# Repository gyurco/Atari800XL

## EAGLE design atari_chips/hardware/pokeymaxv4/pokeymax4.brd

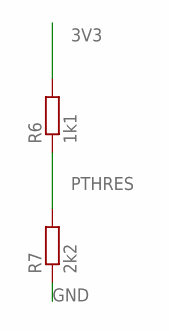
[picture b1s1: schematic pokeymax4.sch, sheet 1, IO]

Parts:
R6: 1k1; R0402
R7: 2k2; R0402

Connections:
3V3: R6.2; also elsewhere on the board
GND: R7.1; also elsewhere on the board
PTHRES: R6.1, R7.2; also elsewhere on the board

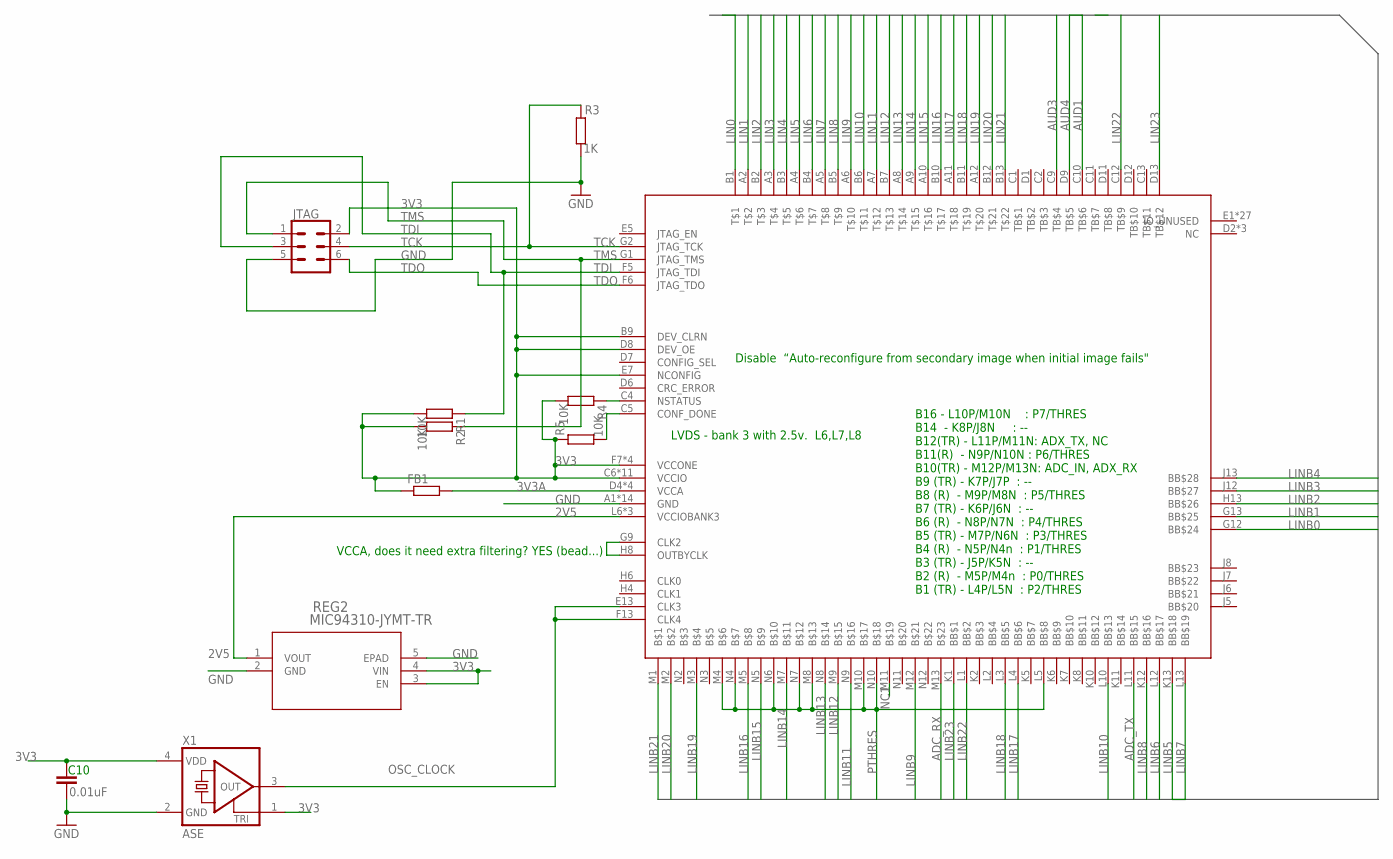
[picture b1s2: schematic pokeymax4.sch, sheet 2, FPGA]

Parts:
C10: 0.01uF; C0402
FB1: R-EU_R0402; R0402
JTAG: CONN_03X2LOCK; 2X3_LOCK
R1, R2, R4, R5: 10K; R0402
R3: 1K; R0402
REG2: MIC94310-JYMT-TR; TDFN4_1P2X1P6_MCH
U3: MAX10; U169SMALL
X1: ASE

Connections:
2V5: REG2.1 (VOUT), U3.L6 (VCCIOBANK3), U3.L7 (VCCIOBANK3), U3.L8 (VCCIOBANK3); also elsewhere on the board
3V3: C10.1, FB1.1, JTAG.2, R1.2, R2.2, R4.2, R5.1, REG2.3 (EN), REG2.4 (VIN), U3.B9 (DEV_CLRN), U3.C6 (VCCIO), U3.C7 (VCCIO), U3.C8 (VCCIO), U3.D8 (DEV_OE), U3.E7 (NCONFIG), U3.F2 (VCCIO), U3.F7 (VCCONE), U3.F11 (VCCIO), U3.G3 (VCCIO), U3.G6 (VCCONE), U3.G8 (VCCONE), U3.G11 (VCCIO), U3.H7 (VCCONE), U3.H11 (VCCIO), U3.J3 (VCCIO), U3.J11 (VCCIO), U3.K3 (VCCIO), X1.1 (TRI), X1.4 (VDD); also elsewhere on the board
3V3A: FB1.2, U3.D4 (VCCA), U3.D10 (VCCA), U3.K4 (VCCA), U3.K9 (VCCA); also elsewhere on the board
ADC_RX: U3.M13; also elsewhere on the board
ADC_TX: U3.L11 (BB$15); also elsewhere on the board
AUD1: U3.C10 (TB$6); also elsewhere on the board
AUD3: U3.C9 (TB$4); also elsewhere on the board
AUD4: U3.D9 (TB$5); also elsewhere on the board
CONF_DONE: R5.2, U3.C5 (CONF_DONE)
FAKE_CLK: U3.G9 (CLK2), U3.H8 (OUTBYCLK)
GND: C10.2, JTAG.5, R3.2, REG2.2 (GND), REG2.5 (EPAD), U3.A1 (GND), U3.A13 (GND), U3.B8 (GND), U3.C3 (GND), U3.D5 (GND), U3.E11 (GND), U3.F3 (GND), U3.G7 (GND), U3.H12 (GND), U3.J4 (GND), U3.L9 (GND), U3.M6 (GND), U3.N1 (GND), U3.N13 (GND), X1.2 (GND); also elsewhere on the board
LIN0: U3.B1; also elsewhere on the board
LIN1: U3.A2; also elsewhere on the board
LIN2: U3.B2; also elsewhere on the board
LIN3: U3.A3; also elsewhere on the board
LIN4: U3.B3; also elsewhere on the board
LIN5: U3.A4; also elsewhere on the board
LIN6: U3.B4; also elsewhere on the board
LIN7: U3.A5; also elsewhere on the board
LIN8: U3.B5; also elsewhere on the board
LIN9: U3.A6; also elsewhere on the board
LIN10: U3.B6; also elsewhere on the board
LIN11: U3.A7; also elsewhere on the board
LIN12: U3.B7; also elsewhere on the board
LIN13: U3.A8; also elsewhere on the board
LIN14: U3.A9; also elsewhere on the board
LIN15: U3.A10; also elsewhere on the board
LIN16: U3.B10; also elsewhere on the board
LIN17: U3.A11; also elsewhere on the board
LIN18: U3.B11; also elsewhere on the board
LIN19: U3.A12; also elsewhere on the board
LIN20: U3.B12; also elsewhere on the board
LIN21: U3.B13; also elsewhere on the board
LIN22: U3.C12 (TB$9); also elsewhere on the board
LIN23: U3.D13 (TB$12); also elsewhere on the board
LINB0: U3.G12 (BB$24); also elsewhere on the board
LINB1: U3.G13 (BB$25); also elsewhere on the board
LINB2: U3.H13 (BB$26); also elsewhere on the board
LINB3: U3.J12 (BB$27); also elsewhere on the board
LINB4: U3.J13 (BB$28); also elsewhere on the board
LINB5: U3.K13 (BB$18); also elsewhere on the board
LINB6: U3.L12 (BB$17); also elsewhere on the board
LINB7: U3.L13 (BB$19); also elsewhere on the board
LINB8: U3.K12 (BB$16); also elsewhere on the board
LINB9: U3.M12; also elsewhere on the board
LINB10: U3.L10 (BB$13); also elsewhere on the board
LINB11: U3.N9; also elsewhere on the board
LINB12: U3.M9; also elsewhere on the board
LINB13: U3.N8; also elsewhere on the board
LINB14: U3.M7; also elsewhere on the board
LINB15: U3.N5; also elsewhere on the board
LINB16: U3.M5; also elsewhere on the board
LINB17: U3.L4 (BB$6); also elsewhere on the board
LINB18: U3.L3 (BB$5); also elsewhere on the board
LINB19: U3.M3; also elsewhere on the board
LINB20: U3.M2; also elsewhere on the board
LINB21: U3.M1; also elsewhere on the board
LINB22: U3.L1 (BB$2); also elsewhere on the board
LINB23: U3.K1 (BB$1); also elsewhere on the board
NC1: U3.M11
NSTATUS: R4.1, U3.C4 (NSTATUS)
OSC_CLOCK: U3.E13 (CLK3), U3.F13 (CLK4), X1.3 (OUT)
PTHRES: U3.L5 (BB$8), U3.M4, U3.M8, U3.M10, U3.N4, U3.N6, U3.N7, U3.N10; also elsewhere on the board
TCK: JTAG.4, R3.1, U3.G2 (JTAG_TCK)
TDI: JTAG.3, R1.1, U3.F5 (JTAG_TDI)
TDO: JTAG.6, U3.F6 (JTAG_TDO)
TMS: JTAG.1, R2.1, U3.G1 (JTAG_TMS)

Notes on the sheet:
VCCA, does it need extra filtering? YES (bead...)
Disable “Auto-reconfigure from secondary image when initial image fails"
LVDS - bank 3 with 2.5v. L6,L7,L8
B16 - L10P/M10N : P7/THRES B14 - K8P/J8N : -- B12(TR) - L11P/M11N: ADX_TX, NC B11(R) - N9P/N10N : P6/THRES B10(TR) - M12P/M13N: ADC_IN, ADX_RX B9 (TR) - K7P/J7P : -- B8 (R) - M9P/M8N : P5/THRES B7 (TR) - K6P/J6N : -- B6 (R) - N8P/N7N : P4/THRES B5 (TR) - M7P/N6N : P3/THRES B4 (R) - N5P/N4n : P1/THR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

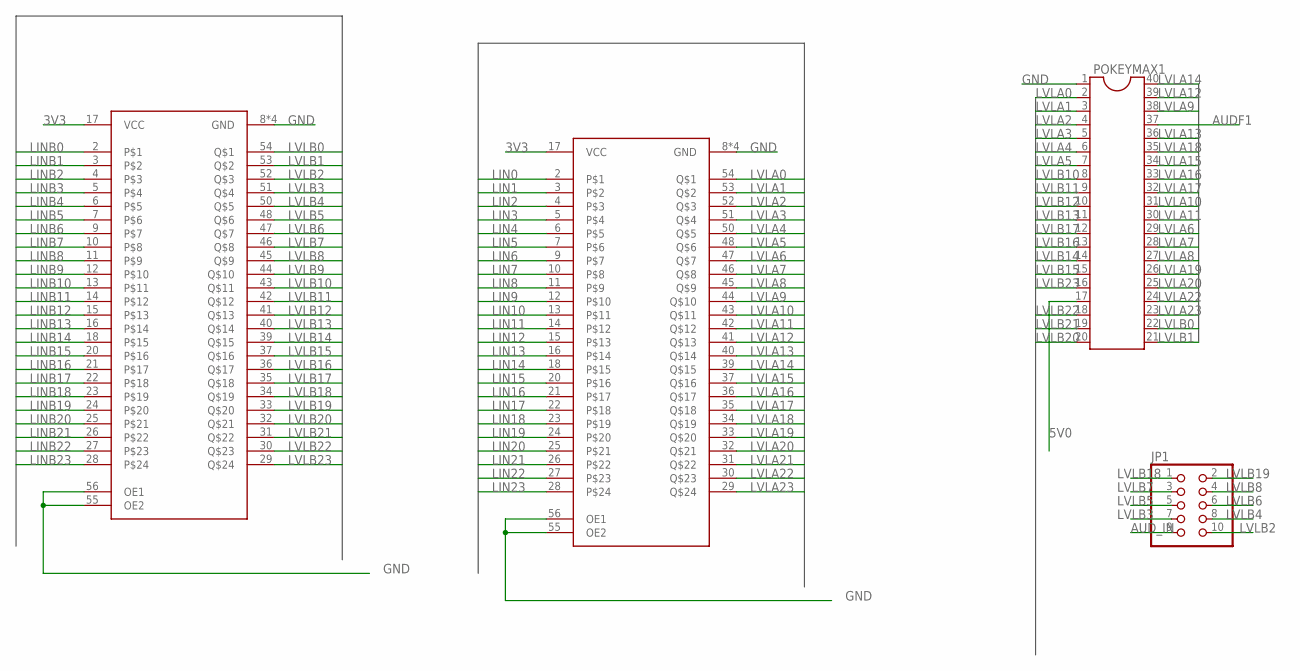
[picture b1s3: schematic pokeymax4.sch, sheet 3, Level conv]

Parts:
JP1: PINHD-2X5; 2X05
POKEYMAX1: DIL40
U2, U4: SN74CB3T16211SM; 56TVSOP_SMALL

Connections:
3V3: U2.17 (VCC), U4.17 (VCC); also elsewhere on the board
5V0: POKEYMAX1.17; also elsewhere on the board
AUDF1: POKEYMAX1.37; also elsewhere on the board
AUD_IN: JP1.9; also elsewhere on the board
GND: POKEYMAX1.1, U2.8 (GND), U2.19 (GND), U2.38 (GND), U2.49 (GND), U2.55 (OE2), U2.56 (OE1), U4.8 (GND), U4.19 (GND), U4.38 (GND), U4.49 (GND), U4.55 (OE2), U4.56 (OE1); also elsewhere on the board
LIN0: U2.2; also elsewhere on the board
LIN1: U2.3; also elsewhere on the board
LIN2: U2.4; also elsewhere on the board
LIN3: U2.5; also elsewhere on the board
LIN4: U2.6; also elsewhere on the board
LIN5: U2.7; also elsewhere on the board
LIN6: U2.9; also elsewhere on the board
LIN7: U2.10; also elsewhere on the board
LIN8: U2.11; also elsewhere on the board
LIN9: U2.12; also elsewhere on the board
LIN10: U2.13; also elsewhere on the board
LIN11: U2.14; also elsewhere on the board
LIN12: U2.15; also elsewhere on the board
LIN13: U2.16; also elsewhere on the board
LIN14: U2.18; also elsewhere on the board
LIN15: U2.20; also elsewhere on the board
LIN16: U2.21; also elsewhere on the board
LIN17: U2.22; also elsewhere on the board
LIN18: U2.23; also elsewhere on the board
LIN19: U2.24; also elsewhere on the board
LIN20: U2.25; also elsewhere on the board
LIN21: U2.26; also elsewhere on the board
LIN22: U2.27; also elsewhere on the board
LIN23: U2.28; also elsewhere on the board
LINB0: U4.2; also elsewhere on the board
LINB1: U4.3; also elsewhere on the board
LINB2: U4.4; also elsewhere on the board
LINB3: U4.5; also elsewhere on the board
LINB4: U4.6; also elsewhere on the board
LINB5: U4.7; also elsewhere on the board
LINB6: U4.9; also elsewhere on the board
LINB7: U4.10; also elsewhere on the board
LINB8: U4.11; also elsewhere on the board
LINB9: U4.12; also elsewhere on the board
LINB10: U4.13; also elsewhere on the board
LINB11: U4.14; also elsewhere on the board
LINB12: U4.15; also elsewhere on the board
LINB13: U4.16; also elsewhere on the board
LINB14: U4.18; also elsewhere on the board
LINB15: U4.20; also elsewhere on the board
LINB16: U4.21; also elsewhere on the board
LINB17: U4.22; also elsewhere on the board
LINB18: U4.23; also elsewhere on the board
LINB19: U4.24; also elsewhere on the board
LINB20: U4.25; also elsewhere on the board
LINB21: U4.26; also elsewhere on the board
LINB22: U4.27; also elsewhere on the board
LINB23: U4.28; also elsewhere on the board
LVLA0: POKEYMAX1.2, U2.54
LVLA1: POKEYMAX1.3, U2.53
LVLA2: POKEYMAX1.4, U2.52
LVLA3: POKEYMAX1.5, U2.51
LVLA4: POKEYMAX1.6, U2.50
LVLA5: POKEYMAX1.7, U2.48
LVLA6: POKEYMAX1.29, U2.47
LVLA7: POKEYMAX1.28, U2.46
LVLA8: POKEYMAX1.27, U2.45
LVLA9: POKEYMAX1.38, U2.44
LVLA10: POKEYMAX1.31, U2.43
LVLA11: POKEYMAX1.30, U2.42
LVLA12: POKEYMAX1.39, U2.41
LVLA13: POKEYMAX1.36, U2.40
LVLA14: POKEYMAX1.40, U2.39
LVLA15: POKEYMAX1.34, U2.37
LVLA16: POKEYMAX1.33, U2.36
LVLA17: POKEYMAX1.32, U2.35
LVLA18: POKEYMAX1.35, U2.34
LVLA19: POKEYMAX1.26, U2.33
LVLA20: POKEYMAX1.25, U2.32
LVLA21: U2.31; also elsewhere on the board
LVLA22: POKEYMAX1.24, U2.30
LVLA23: POKEYMAX1.23, U2.29
LVLB0: POKEYMAX1.22, U4.54
LVLB1: POKEYMAX1.21, U4.53
LVLB2: JP1.10, U4.52
LVLB3: JP1.7, U4.51
LVLB4: JP1.8, U4.50
LVLB5: JP1.5, U4.48
LVLB6: JP1.6, U4.47
LVLB7: JP1.3, U4.46
LVLB8: JP1.4, U4.45
LVLB9: U4.44; also elsewhere on the board
LVLB10: POKEYMAX1.8, U4.43
LVLB11: POKEYMAX1.9, U4.42
LVLB12: POKEYMAX1.10, U4.41
LVLB13: POKEYMAX1.11, U4.40
LVLB14: POKEYMAX1.14, U4.39
LVLB15: POKEYMAX1.15, U4.37
LVLB16: POKEYMAX1.13, U4.36
LVLB17: POKEYMAX1.12, U4.35
LVLB18: JP1.1, U4.34
LVLB19: JP1.2, U4.33
LVLB20: POKEYMAX1.20, U4.32
LVLB21: POKEYMAX1.19, U4.31
LVLB22: POKEYMAX1.18, U4.30
LVLB23: POKEYMAX1.16, U4.29

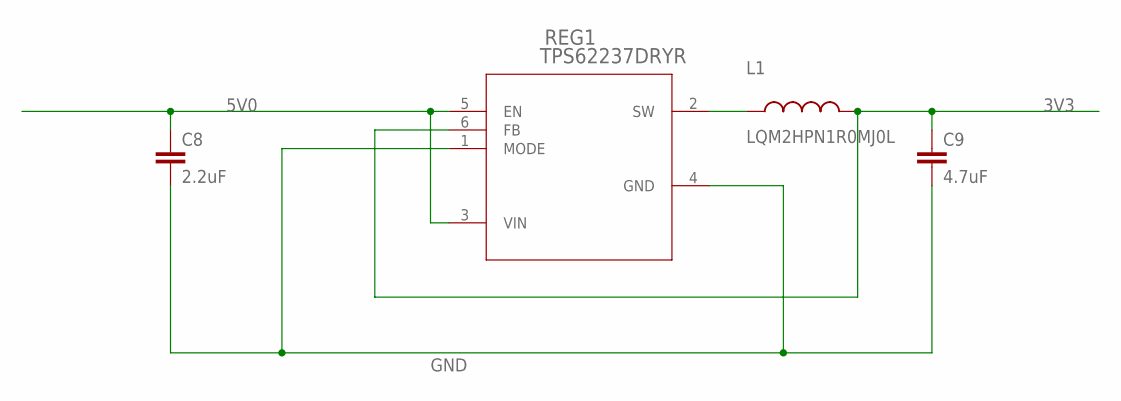
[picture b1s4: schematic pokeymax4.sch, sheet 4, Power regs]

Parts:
C8: 2.2uF; C0402
C9: 4.7uF; C0402
L1: LQM2HPN1R0MJ0L; INDC1008X04
REG1: TPS62237DRYR; DRY6

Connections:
3V3: C9.1, L1.2, REG1.6 (FB); also elsewhere on the board
5V0: C8.1, REG1.3 (VIN), REG1.5 (EN); also elsewhere on the board
GND: C8.2, C9.2, REG1.1 (MODE), REG1.4 (GND); also elsewhere on the board
unnamed: L1.1, REG1.2 (SW)

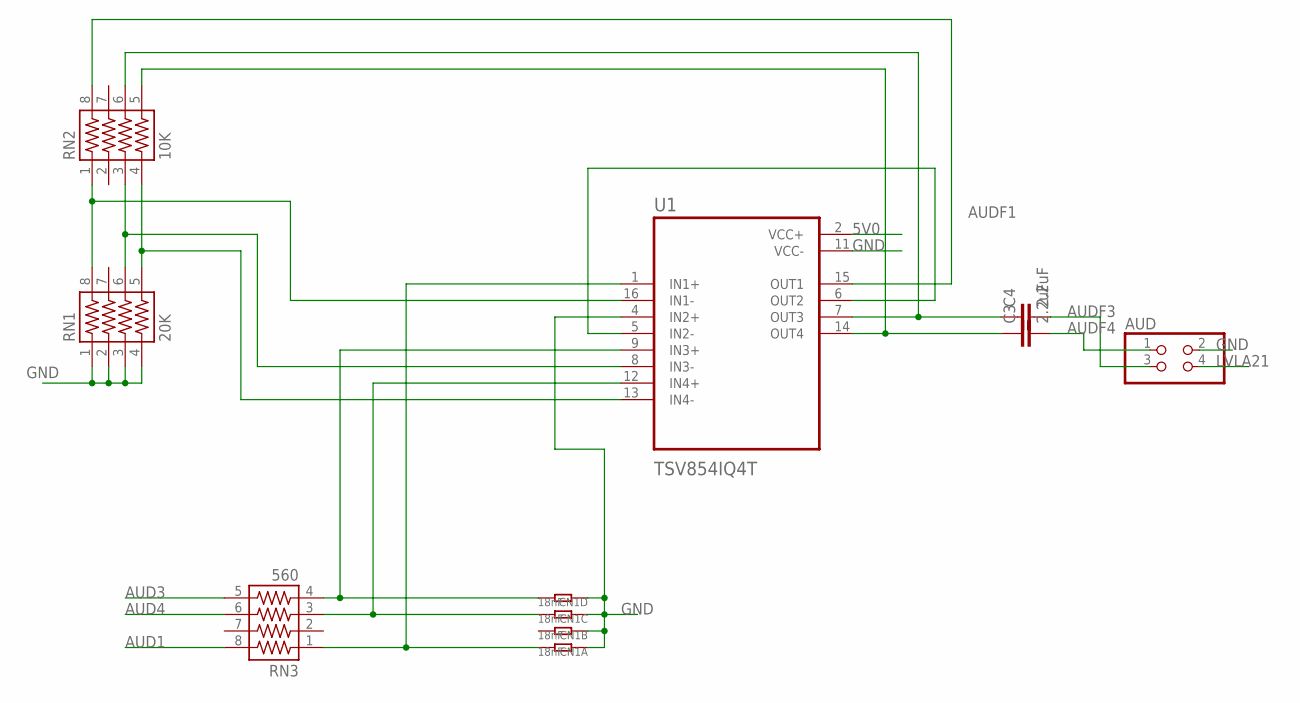
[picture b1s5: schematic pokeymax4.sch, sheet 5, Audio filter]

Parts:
AUD: PINHD-2X2; 2X02
C3, C4: 2.2uF; C0402
CN1: 18nF; R1206-8
RN1: 20K; 741-8
RN2: 10K; 741-8
RN3: 560; 741-8
U1: TSV854IQ4T; QFN50P300X300X100-16N

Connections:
5V0: U1.2 (VCC+); also elsewhere on the board
AMPIN1M: RN1.8, RN2.1, U1.16 (IN1-)
AMPIN1P: CN1.8 (2), RN3.1, U1.1 (IN1+)
AMPIN3M: RN1.6, RN2.3, U1.8 (IN3-)
AMPIN3P: CN1.5 (2), RN3.4, U1.9 (IN3+)
AMPIN4P: CN1.6 (2), RN3.3, U1.12 (IN4+)
AUD1: RN3.8; also elsewhere on the board
AUD3: RN3.5; also elsewhere on the board
AUD4: RN3.6; also elsewhere on the board
AUDF1: RN2.8, U1.15 (OUT1); also elsewhere on the board
AUDF2: U1.5 (IN2-), U1.6 (OUT2)
AUDF3: AUD.3, C4.2
AUDF4: AUD.1, C3.2
GND: AUD.2, CN1.1, CN1.2 (1), CN1.3 (1), CN1.4 (1), RN1.1, RN1.2, RN1.3, RN1.4, U1.4 (IN2+), U1.11 (VCC-); also elsewhere on the board
LVLA21: AUD.4; also elsewhere on the board
unnamed: C3.1, RN2.5, U1.14 (OUT4)
unnamed: C4.1, RN2.6, U1.7 (OUT3)
unnamed: RN1.5, RN2.4, U1.13 (IN4-)

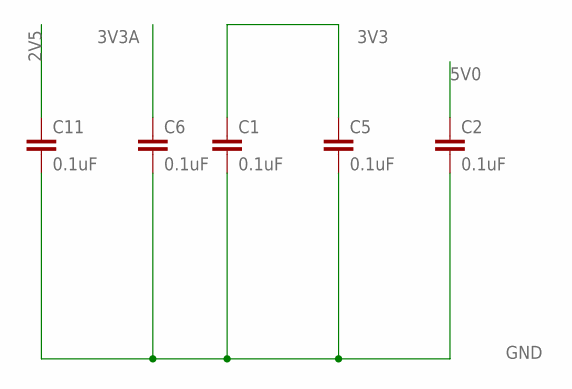
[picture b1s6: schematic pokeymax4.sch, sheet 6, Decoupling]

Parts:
C1, C2, C5, C6, C11: 0.1uF; C0402

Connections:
2V5: C11.1; also elsewhere on the board
3V3: C1.1, C5.1; also elsewhere on the board
3V3A: C6.1; also elsewhere on the board
5V0: C2.1; also elsewhere on the board
GND: C1.2, C2.2, C5.2, C6.2, C11.2; also elsewhere on the board

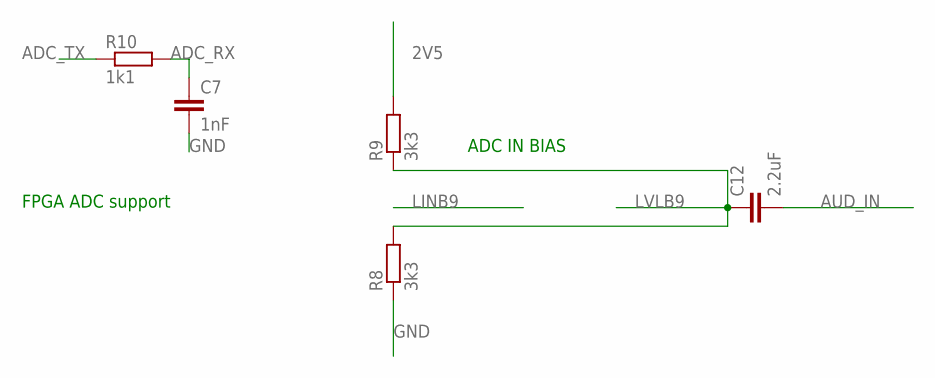
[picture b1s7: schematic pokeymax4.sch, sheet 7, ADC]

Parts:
C7: 1nF; C0402
C12: 2.2uF; C0402
R8, R9: 3k3; R0402
R10: 1k1; R0402

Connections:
2V5: R9.2; also elsewhere on the board
ADC_RX: C7.1, R10.2; also elsewhere on the board
ADC_TX: R10.1; also elsewhere on the board
AUD_IN: C12.2; also elsewhere on the board
GND: C7.2, R8.1; also elsewhere on the board
LVLB9: C12.1, R8.2, R9.1; also elsewhere on the board

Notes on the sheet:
ADC IN BIAS
FPGA ADC support

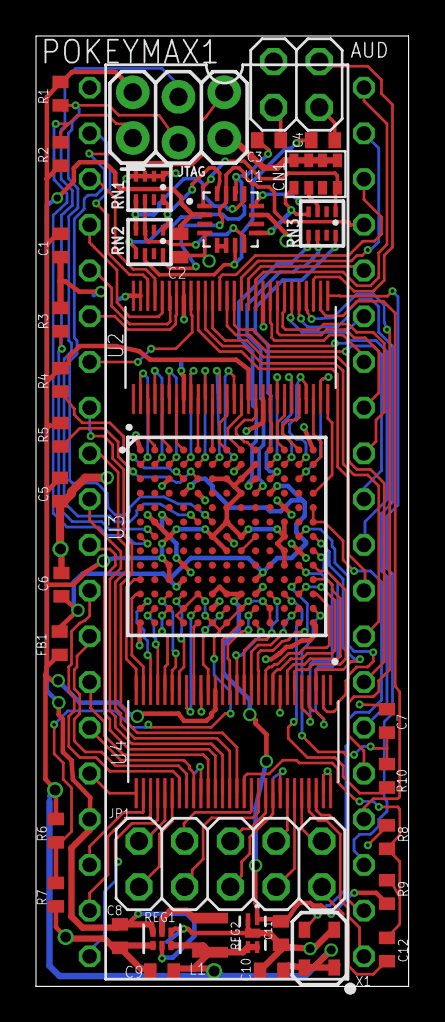
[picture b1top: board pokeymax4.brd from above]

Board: 4 copper layers, 20.7 x 52.8 mm, 39 parts (0 on the bottom side), 129 nets.

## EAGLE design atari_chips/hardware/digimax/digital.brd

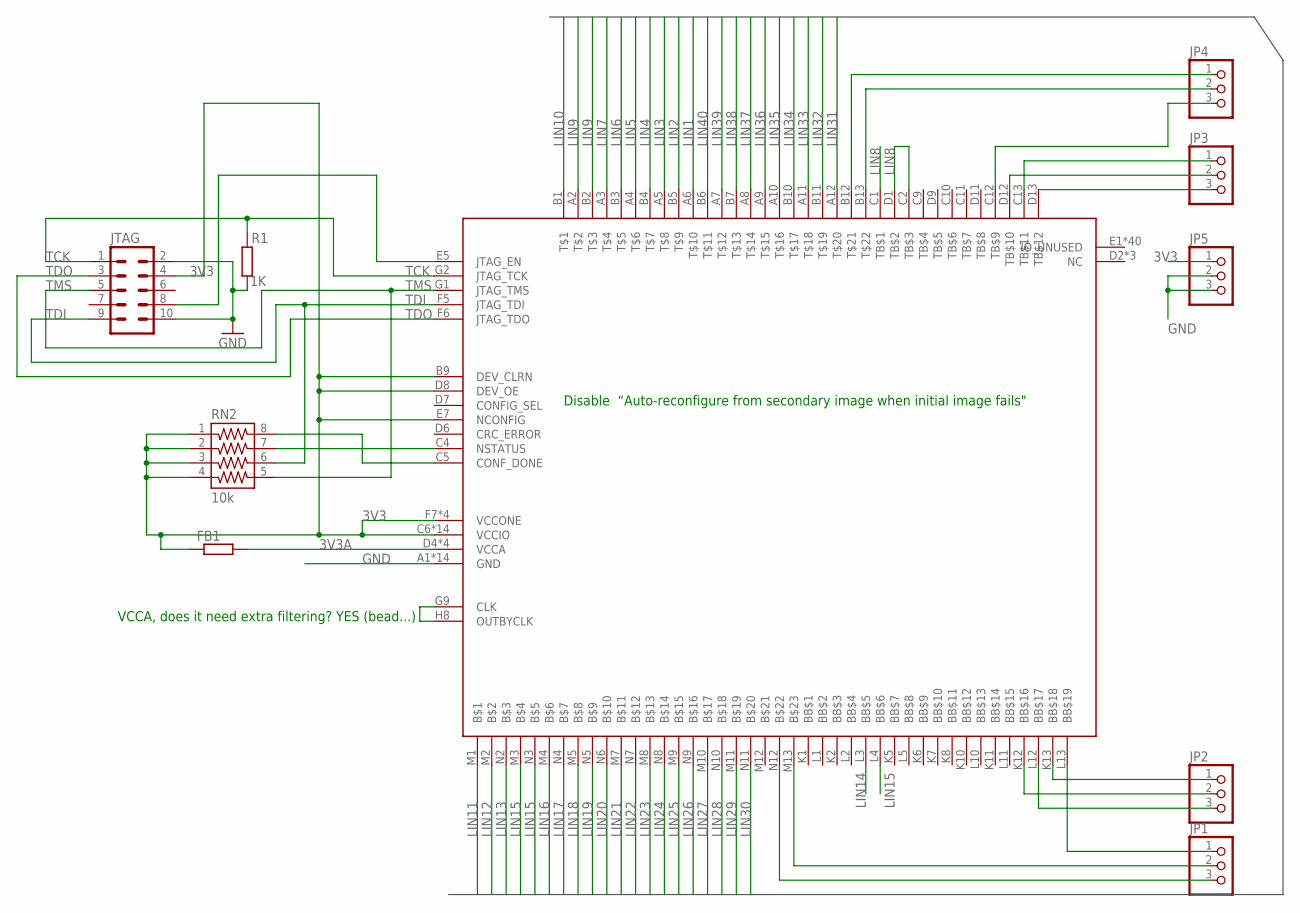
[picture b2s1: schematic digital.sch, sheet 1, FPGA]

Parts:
FB1: R-EU_R0603; R0603
JP1, JP2, JP3, JP4, JP5: PINHD-1X3; 1X03
JTAG: ML10
MAX10: MAX10; U169SMALL
R1: 1K; R0603
RN2: 10k; 742-8

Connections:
3V3: FB1.1, JP5.1, JTAG.4, MAX10.B9 (DEV_CLRN), MAX10.C6 (VCCIO), MAX10.C7 (VCCIO), MAX10.C8 (VCCIO), MAX10.D8 (DEV_OE), MAX10.E7 (NCONFIG), MAX10.F2 (VCCIO), MAX10.F7 (VCCONE), MAX10.F11 (VCCIO), MAX10.G3 (VCCIO), MAX10.G6 (VCCONE), MAX10.G8 (VCCONE), MAX10.G11 (VCCIO), MAX10.H7 (VCCONE), MAX10.H11 (VCCIO), MAX10.J3 (VCCIO), MAX10.J11 (VCCIO), MAX10.K3 (VCCIO), MAX10.L6 (VCCIO), MAX10.L7 (VCCIO), MAX10.L8 (VCCIO), RN2.1, RN2.2, RN2.3, RN2.4; also elsewhere on the board
3V3A: FB1.2, MAX10.D4 (VCCA), MAX10.D10 (VCCA), MAX10.K4 (VCCA), MAX10.K9 (VCCA); also elsewhere on the board
CONF_DONE: MAX10.C5 (CONF_DONE), RN2.8
FAKE_CLK: MAX10.G9 (CLK), MAX10.H8 (OUTBYCLK)
GND: JP5.2, JP5.3, JTAG.2, JTAG.10, MAX10.A1 (GND), MAX10.A13 (GND), MAX10.B8 (GND), MAX10.C3 (GND), MAX10.D5 (GND), MAX10.E11 (GND), MAX10.F3 (GND), MAX10.G7 (GND), MAX10.H12 (GND), MAX10.J4 (GND), MAX10.L9 (GND), MAX10.M6 (GND), MAX10.N1 (GND), MAX10.N13 (GND), R1.2; also elsewhere on the board
JTAGEN: JTAG.8, MAX10.E5 (JTAG_EN)
LIN1: MAX10.A6; also elsewhere on the board
LIN2: MAX10.B5; also elsewhere on the board
LIN3: MAX10.A5; also elsewhere on the board
LIN4: MAX10.B4; also elsewhere on the board
LIN5: MAX10.A4; also elsewhere on the board
LIN6: MAX10.B3; also elsewhere on the board
LIN7: MAX10.A3; also elsewhere on the board
LIN8: MAX10.C1 (TB$1), MAX10.C2 (TB$3), MAX10.D1 (TB$2); also elsewhere on the board
LIN9: MAX10.A2, MAX10.B2; also elsewhere on the board
LIN10: MAX10.B1; also elsewhere on the board
LIN11: MAX10.M1; also elsewhere on the board
LIN12: MAX10.M2; also elsewhere on the board
LIN13: MAX10.N2; also elsewhere on the board
LIN14: MAX10.L3 (BB$5); also elsewhere on the board
LIN15: MAX10.L4 (BB$6), MAX10.M3, MAX10.N3; also elsewhere on the board
LIN16: MAX10.M4; also elsewhere on the board
LIN17: MAX10.N4; also elsewhere on the board
LIN18: MAX10.M5; also elsewhere on the board
LIN19: MAX10.N5; also elsewhere on the board
LIN20: MAX10.N6; also elsewhere on the board
LIN21: MAX10.M7; also elsewhere on the board
LIN22: MAX10.N7; also elsewhere on the board
LIN23: MAX10.M8; also elsewhere on the board
LIN24: MAX10.N8; also elsewhere on the board
LIN25: MAX10.M9; also elsewhere on the board
LIN26: MAX10.N9; also elsewhere on the board
LIN27: MAX10.M10; also elsewhere on the board
LIN28: MAX10.N10; also elsewhere on the board
LIN29: MAX10.M11; also elsewhere on the board
LIN30: MAX10.N11; also elsewhere on the board
LIN31: MAX10.A12; also elsewhere on the board
LIN32: MAX10.B11; also elsewhere on the board
LIN33: MAX10.A11; also elsewhere on the board
LIN34: MAX10.B10; also elsewhere on the board
LIN35: MAX10.A10; also elsewhere on the board
LIN36: MAX10.A9; also elsewhere on the board
LIN37: MAX10.A8; also elsewhere on the board
LIN38: MAX10.B7; also elsewhere on the board
LIN39: MAX10.A7; also elsewhere on the board
LIN40: MAX10.B6; also elsewhere on the board
unnamed: JP2.2, MAX10.K12 (BB$16)
unnamed: JP1.3, MAX10.N12
unnamed: JP1.2, MAX10.M13
unnamed: JP2.1, MAX10.K13 (BB$18)
unnamed: JP2.3, MAX10.L12 (BB$17)
unnamed: JP1.1, MAX10.L13 (BB$19)
unnamed: JP3.3, MAX10.D13 (TB$12)
unnamed: JP3.1, MAX10.C13 (TB$11)
unnamed: JP3.2, MAX10.D12 (TB$10)
unnamed: JP4.3, MAX10.C12 (TB$9)
unnamed: JP4.2, MAX10.B13
unnamed: JP4.1, MAX10.B12
NSTATUS: MAX10.C4 (NSTATUS), RN2.7
TCK: JTAG.1, MAX10.G2 (JTAG_TCK), R1.1
TDI: JTAG.9, MAX10.F5 (JTAG_TDI), RN2.6
TDO: JTAG.3, MAX10.F6 (JTAG_TDO)
TMS: JTAG.5, MAX10.G1 (JTAG_TMS), RN2.5

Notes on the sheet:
VCCA, does it need extra filtering? YES (bead...)
Disable “Auto-reconfigure from secondary image when initial image fails"

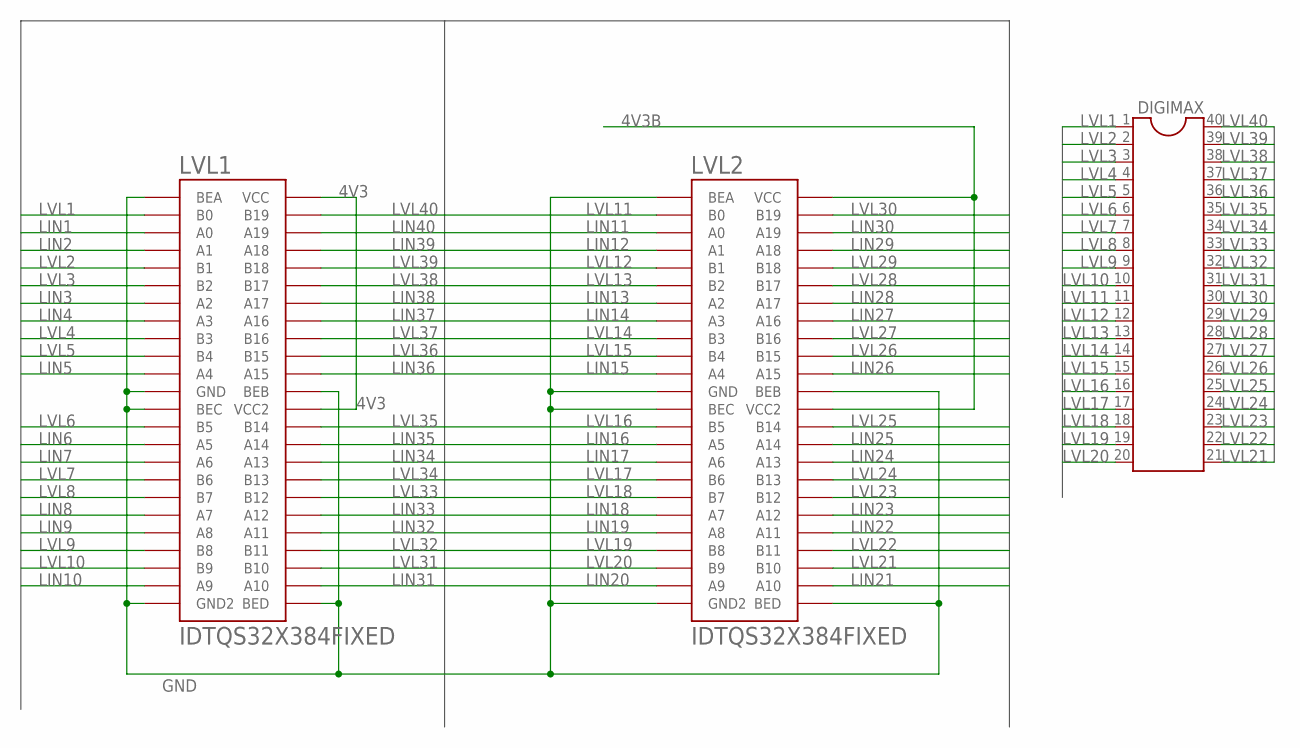
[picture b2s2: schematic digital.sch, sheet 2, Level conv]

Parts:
DIGIMAX: DIL40
LVL1, LVL2: IDTQS32X384FIXED; IDTQS32X384_04MM

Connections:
4V3: LVL1.P$36 (VCC2), LVL1.P$48 (VCC); also elsewhere on the board
4V3B: LVL2.P$36 (VCC2), LVL2.P$48 (VCC); also elsewhere on the board
GND: LVL1.P$1 (BEA), LVL1.P$12 (GND), LVL1.P$13 (BEC), LVL1.P$24 (GND2), LVL1.P$25 (BED), LVL1.P$37 (BEB), LVL2.P$1 (BEA), LVL2.P$12 (GND), LVL2.P$13 (BEC), LVL2.P$24 (GND2), LVL2.P$25 (BED), LVL2.P$37 (BEB); also elsewhere on the board
LIN1: LVL1.P$3 (A0); also elsewhere on the board
LIN2: LVL1.P$4 (A1); also elsewhere on the board
LIN3: LVL1.P$7 (A2); also elsewhere on the board
LIN4: LVL1.P$8 (A3); also elsewhere on the board
LIN5: LVL1.P$11 (A4); also elsewhere on the board
LIN6: LVL1.P$15 (A5); also elsewhere on the board
LIN7: LVL1.P$16 (A6); also elsewhere on the board
LIN8: LVL1.P$19 (A7); also elsewhere on the board
LIN9: LVL1.P$20 (A8); also elsewhere on the board
LIN10: LVL1.P$23 (A9); also elsewhere on the board
LIN11: LVL2.P$3 (A0); also elsewhere on the board
LIN12: LVL2.P$4 (A1); also elsewhere on the board
LIN13: LVL2.P$7 (A2); also elsewhere on the board
LIN14: LVL2.P$8 (A3); also elsewhere on the board
LIN15: LVL2.P$11 (A4); also elsewhere on the board
LIN16: LVL2.P$15 (A5); also elsewhere on the board
LIN17: LVL2.P$16 (A6); also elsewhere on the board
LIN18: LVL2.P$19 (A7); also elsewhere on the board
LIN19: LVL2.P$20 (A8); also elsewhere on the board
LIN20: LVL2.P$23 (A9); also elsewhere on the board
LIN21: LVL2.P$26 (A10); also elsewhere on the board
LIN22: LVL2.P$29 (A11); also elsewhere on the board
LIN23: LVL2.P$30 (A12); also elsewhere on the board
LIN24: LVL2.P$33 (A13); also elsewhere on the board
LIN25: LVL2.P$34 (A14); also elsewhere on the board
LIN26: LVL2.P$38 (A15); also elsewhere on the board
LIN27: LVL2.P$41 (A16); also elsewhere on the board
LIN28: LVL2.P$42 (A17); also elsewhere on the board
LIN29: LVL2.P$45 (A18); also elsewhere on the board
LIN30: LVL2.P$46 (A19); also elsewhere on the board
LIN31: LVL1.P$26 (A10); also elsewhere on the board
LIN32: LVL1.P$29 (A11); also elsewhere on the board
LIN33: LVL1.P$30 (A12); also elsewhere on the board
LIN34: LVL1.P$33 (A13); also elsewhere on the board
LIN35: LVL1.P$34 (A14); also elsewhere on the board
LIN36: LVL1.P$38 (A15); also elsewhere on the board
LIN37: LVL1.P$41 (A16); also elsewhere on the board
LIN38: LVL1.P$42 (A17); also elsewhere on the board
LIN39: LVL1.P$45 (A18); also elsewhere on the board
LIN40: LVL1.P$46 (A19); also elsewhere on the board
LVL1: DIGIMAX.1, LVL1.P$2 (B0)
LVL2: DIGIMAX.2, LVL1.P$5 (B1)
LVL3: DIGIMAX.3, LVL1.P$6 (B2)
LVL4: DIGIMAX.4, LVL1.P$9 (B3)
LVL5: DIGIMAX.5, LVL1.P$10 (B4)
LVL6: DIGIMAX.6, LVL1.P$14 (B5)
LVL7: DIGIMAX.7, LVL1.P$17 (B6)
LVL8: DIGIMAX.8, LVL1.P$18 (B7)
LVL9: DIGIMAX.9, LVL1.P$21 (B8)
LVL10: DIGIMAX.10, LVL1.P$22 (B9)
LVL11: DIGIMAX.11, LVL2.P$2 (B0)
LVL12: DIGIMAX.12, LVL2.P$5 (B1)
LVL13: DIGIMAX.13, LVL2.P$6 (B2)
LVL14: DIGIMAX.14, LVL2.P$9 (B3)
LVL15: DIGIMAX.15, LVL2.P$10 (B4)
LVL16: DIGIMAX.16, LVL2.P$14 (B5)
LVL17: DIGIMAX.17, LVL2.P$17 (B6)
LVL18: DIGIMAX.18, LVL2.P$18 (B7)
LVL19: DIGIMAX.19, LVL2.P$21 (B8)
LVL20: DIGIMAX.20, LVL2.P$22 (B9)
LVL21: DIGIMAX.21, LVL2.P$27 (B10)
LVL22: DIGIMAX.22, LVL2.P$28 (B11)
LVL23: DIGIMAX.23, LVL2.P$31 (B12)
LVL24: DIGIMAX.24, LVL2.P$32 (B13)
LVL25: DIGIMAX.25, LVL2.P$35 (B14)
LVL26: DIGIMAX.26, LVL2.P$39 (B15)
LVL27: DIGIMAX.27, LVL2.P$40 (B16)
LVL28: DIGIMAX.28, LVL2.P$43 (B17)
LVL29: DIGIMAX.29, LVL2.P$44 (B18)
LVL30: DIGIMAX.30, LVL2.P$47 (B19)
LVL31: DIGIMAX.31, LVL1.P$27 (B10)
LVL32: DIGIMAX.32, LVL1.P$28 (B11)
LVL33: DIGIMAX.33, LVL1.P$31 (B12)
LVL34: DIGIMAX.34, LVL1.P$32 (B13)
LVL35: DIGIMAX.35, LVL1.P$35 (B14)
LVL36: DIGIMAX.36, LVL1.P$39 (B15)
LVL37: DIGIMAX.37, LVL1.P$40 (B16)
LVL38: DIGIMAX.38, LVL1.P$43 (B17)
LVL39: DIGIMAX.39, LVL1.P$44 (B18)
LVL40: DIGIMAX.40, LVL1.P$47 (B19)

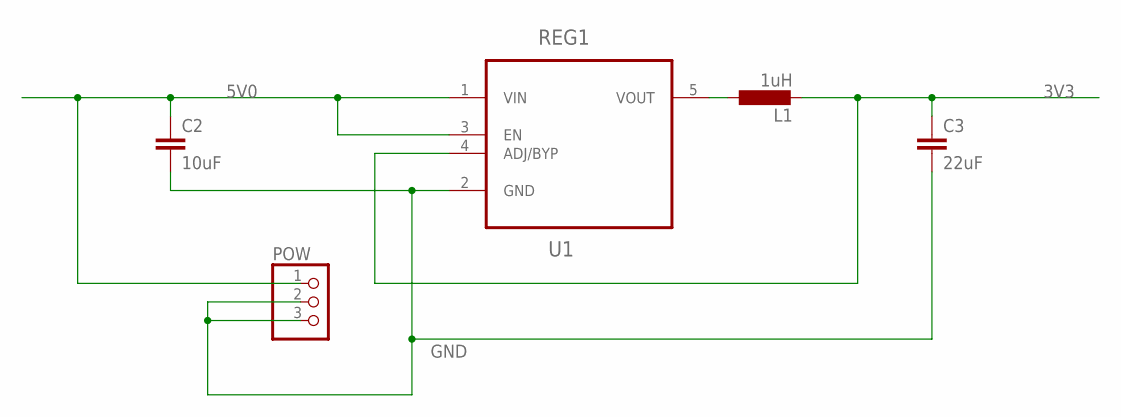
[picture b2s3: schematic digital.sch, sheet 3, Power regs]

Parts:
C2: 10uF; C0805
C3: 22uF; C0805
L1: 1uH; L3225M
POW: PINHD-1X3; 1X03
REG1: U1; SOT95P280X145-5N

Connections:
3V3: C3.1, L1.2, REG1.4 (ADJ/BYP); also elsewhere on the board
5V0: C2.1, POW.1, REG1.1 (VIN), REG1.3 (EN); also elsewhere on the board
GND: C2.2, C3.2, POW.2, POW.3, REG1.2 (GND); also elsewhere on the board
unnamed: L1.1, REG1.5 (VOUT)

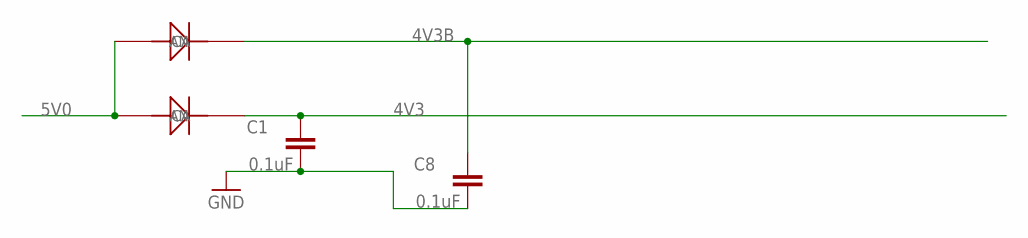
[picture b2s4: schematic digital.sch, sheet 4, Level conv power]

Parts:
C1, C8: 0.1uF; C0603
D1, D2: 1N4148; SOD123

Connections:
4V3: C1.2, D1.1 (CA); also elsewhere on the board
4V3B: C8.2, D2.1 (CA); also elsewhere on the board
5V0: D1.2 (AN), D2.2 (AN); also elsewhere on the board
GND: C1.1, C8.1; also elsewhere on the board

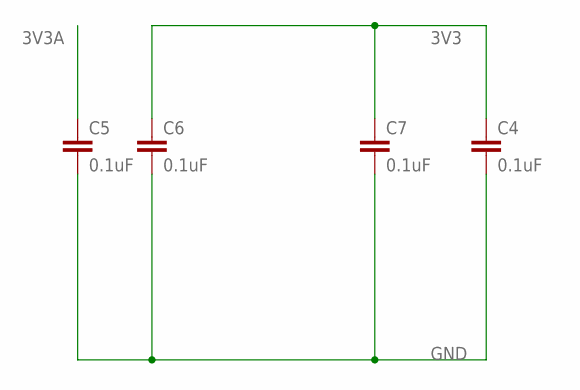
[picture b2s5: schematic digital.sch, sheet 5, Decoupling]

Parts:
C4, C5, C6, C7: 0.1uF; C0603

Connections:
3V3: C4.1, C6.1, C7.1; also elsewhere on the board
3V3A: C5.1; also elsewhere on the board
GND: C4.2, C5.2, C6.2, C7.2; also elsewhere on the board

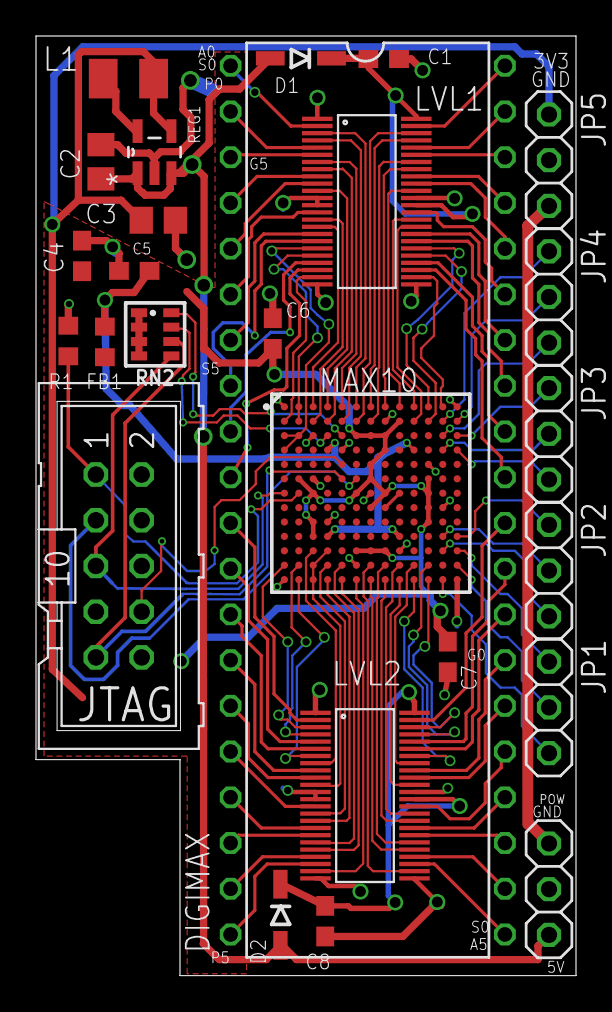
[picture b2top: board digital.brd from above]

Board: 2 copper layers, 30.0 x 52.2 mm, 26 parts (0 on the bottom side), 107 nets.

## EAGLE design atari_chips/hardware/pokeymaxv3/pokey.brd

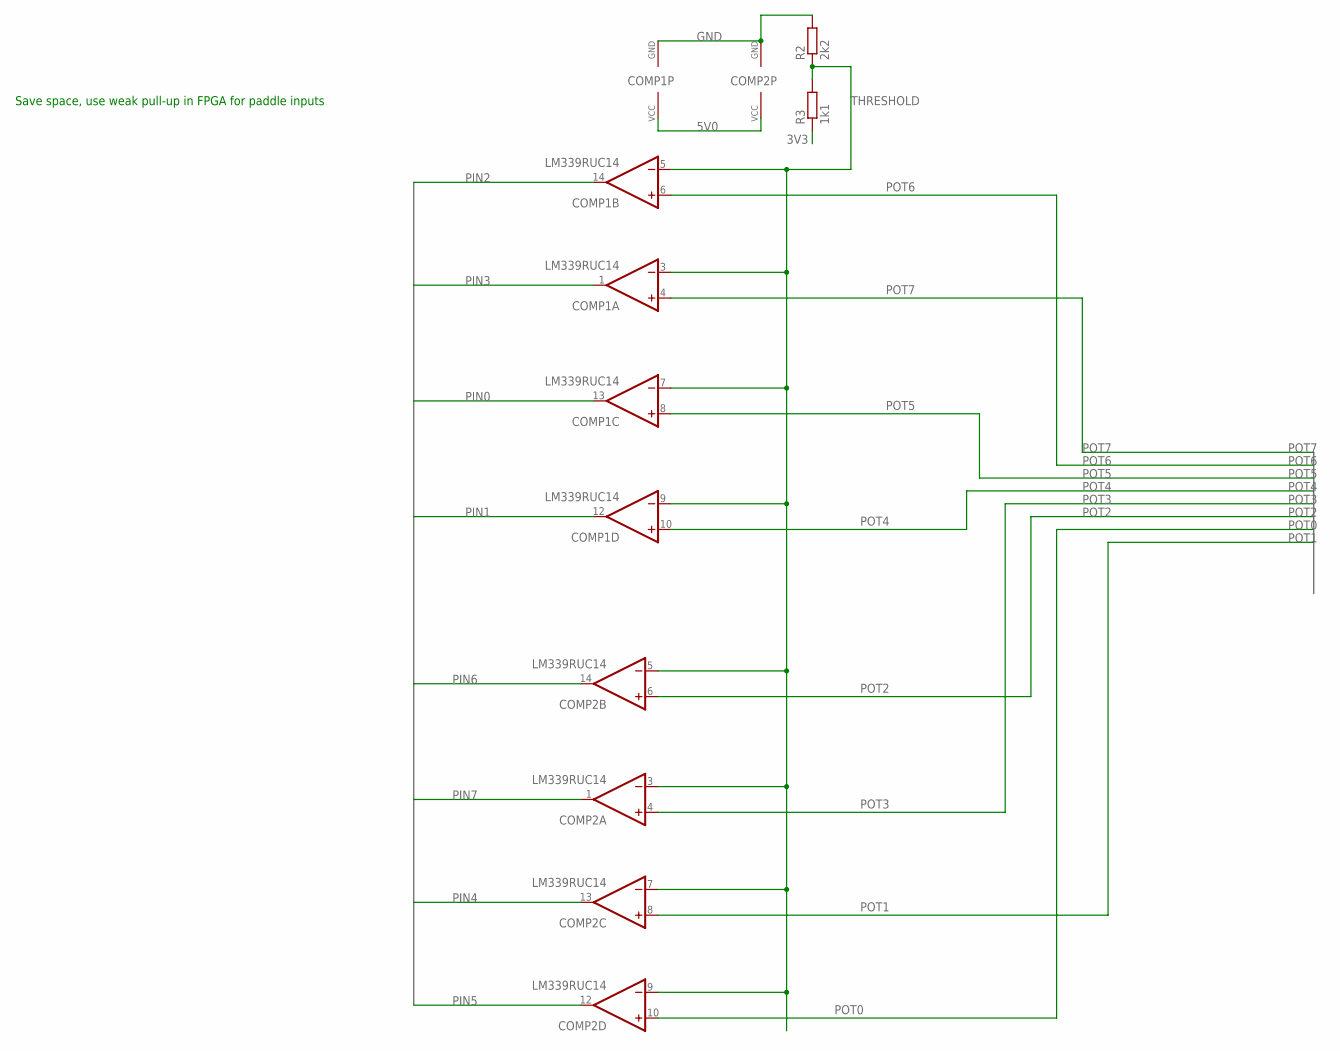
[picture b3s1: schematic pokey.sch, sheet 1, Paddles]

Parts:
COMP1, COMP2: LM339RUC14; RUC14
R2: 2k2; R0402
R3: 1k1; R0402

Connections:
3V3: R3.1; also elsewhere on the board
5V0: COMP1.2 (VCC), COMP2.2 (VCC); also elsewhere on the board
GND: COMP1.11 (GND), COMP2.11 (GND), R2.2; also elsewhere on the board
PIN0: COMP1.13 (OUT); also elsewhere on the board
PIN1: COMP1.12 (OUT); also elsewhere on the board
PIN2: COMP1.14 (OUT); also elsewhere on the board
PIN3: COMP1.1 (OUT); also elsewhere on the board
PIN4: COMP2.13 (OUT); also elsewhere on the board
PIN5: COMP2.12 (OUT); also elsewhere on the board
PIN6: COMP2.14 (OUT); also elsewhere on the board
PIN7: COMP2.1 (OUT); also elsewhere on the board
POT0: COMP2.10 (+IN); also elsewhere on the board
POT1: COMP2.8 (+IN); also elsewhere on the board
POT2: COMP2.6 (+IN); also elsewhere on the board
POT3: COMP2.4 (+IN); also elsewhere on the board
POT4: COMP1.10 (+IN); also elsewhere on the board
POT5: COMP1.8 (+IN); also elsewhere on the board
POT6: COMP1.6 (+IN); also elsewhere on the board
POT7: COMP1.4 (+IN); also elsewhere on the board
THRESHOLD: COMP1.3 (-IN), COMP1.5 (-IN), COMP1.7 (-IN), COMP1.9 (-IN), COMP2.3 (-IN), COMP2.5 (-IN), COMP2.7 (-IN), COMP2.9 (-IN), R2.1, R3.2

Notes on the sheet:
Save space, use weak pull-up in FPGA for paddle inputs

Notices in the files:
eclaireXL_ITX/hardware/eagle_project/eclaire XL new.brd:
(c)2016 by Mark Watson
parts and their libraries:
resistor-array: Copyright (C) 2008, Bob Starr
SparkFun-Connectors: Licensing: Creative Commons ShareAlike 4.0 International - https://creativecommons.org/licenses/by-sa/4.0
COPYRIGHT: Copyright (C) 2018 Accelerated Designs. All rights reserved
